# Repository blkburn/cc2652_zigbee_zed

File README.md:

# Zigbee End Device based on the CC2652R1

This is the complete hardware and software design of a zigbee end device (ZED) designed to be run from a same CR2032 button cell battery.

Texas Instruments Code Composer and the Simplelink SDK is used for development; based on the zed_temperaturesensor_CC26X2R1_LAUNCHXL_tirtos_ccs project.

The hardware design replicates the Launchpad-CC26x2R1 development board as much as possible.

The CC2652R1 is an ultra-low power ARM Cortex process with support for a number of wireless protocols, such as; Thread, Zigbee®, Bluetooth® 5.1 Low Energy, IEEE 802.15.4, IPv6-enabled (6LoWPAN), as well as proprietary protocols including TI 15.4-Stack (2.4 GHz), and simultaneous multi-protocol operation via Dynamic Multiprotocol Manager (DMM).

Development baord power consuption is in line with published datasheet power comsumption figures, allowing the zigbee end device to last many months or years on a single CR2032 battery.

The development board can interface various I2C sensors; a pin breakout is provided to interface the many cheap sensors available on-line. An Adafruit 4-pin STEMMA connector is also provide to connect to an I2C device in their range.

A JTAG header is provided to interface XDS110 (or better) debuggers. A CC1352 Launchpad with built-in XDS110 has been used to debug the development boards.

4-pin bootloader

## Master branch is currently built with:
* CCStudio version: 10.1.1.00004 
* Simplelink_cc13x2_26x2_sdk_4_30_00_54

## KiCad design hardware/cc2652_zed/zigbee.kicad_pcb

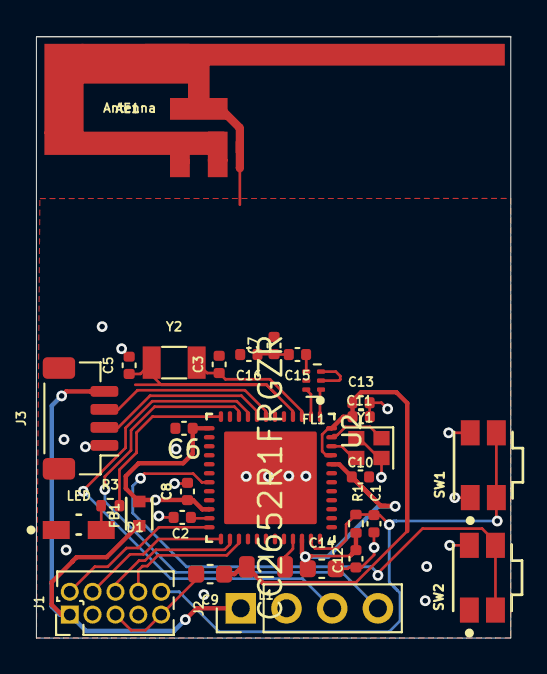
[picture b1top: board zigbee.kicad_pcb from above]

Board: 4 copper layers, 26.3 x 33.4 mm, 31 parts (1 on the bottom side), 27 nets.

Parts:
AE1: Antenna; 2.4GHz-INVERTED-F-ANTENNA
BT1: BAT-HLD-001; Linx-BAT-HLD-001-0
C1, C6, C8, C10, C11, C12, C13: 100n; C_0402_1005Metric
C2, C3, C5: 12p; C_0402_1005Metric
C7, C15, C16: CAP; C_0402_1005Metric
C9, C14: 22u; C_0603_1608Metric
D1: LED; Lite-On-LTST-S220KRKT-0-0-0
FB1: BLM18HE152SN1D; Murata-BLM18-0.15-t0.8-0-0-MFG
FL1: 2450BM14G; Balun_Johanson_1.6x0.8mm
J1: Conn_02x05_Odd_Even; PinHeader_2x05_P1.27mm_Vertical
J2: Conn_01x04; PinHeader_1x04_P2.54mm_Vertical
J3: Conn_01x04; JST_SH_BM04B-SRSS-TB_1x04-1MP_P1.00mm_Vertical
L1: L; L_0805_2012Metric
R1: 100k; R_0402_1005Metric
R3: 150; R_0402_1005Metric
SW1, SW2: EVQ-P7A01P-switch2; Panasonic-EVQ-P7A01P-0-0-MFG
U2: CC2652R1FRGZR; Texas_Instruments-CC2652R1FRGZR-MFG
Y1: Crystal_GND24; Crystal_SMD_2016-4Pin_2.0x1.6mm
Y2: Crystal; Crystal_SMD_3215-2Pin_3.2x1.5mm

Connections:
/DCDC_SW: L1.1, U2.33
/GLED: R3.2, U2.12
/RXD: J3.3, U2.7
/SCL: J2.3, U2.9
/SDA: J2.4, U2.10
/TCKC: J1.4, U2.25
/TDI: J1.8, U2.27
/TDO: J1.6, U2.26
/TMSC: J1.2, U2.24
/TXD: J3.2, U2.8
/X32K_Q1: C3.1, U2.3, Y2.1
/X32K_Q2: C5.1, U2.4, Y2.2
/nReset: C1.1, J1.10, R1.2, SW1.2, SW1.2', U2.35
GND: AE1.2, BT1.1, C1.2, C2.1, C3.2, C5.2, C6.2, C7.2, C8.2, C9.2, C10.2, C11.2, C12.2, C13.2, C14.2, D1.1, FL1.5, FL1.6, J1.3, J1.5, J1.9, J2.2, J3.1, SW1.1, SW1.1', SW2.1, SW2.1', U2.49, Y1.2, Y1.4
unnamed: AE1.1, C16.2
unnamed: C2.2, U2.23
unnamed: C15.1, FL1.1
unnamed: C7.1, C15.2, C16.1
unnamed: D1.2, R3.1
unnamed: FL1.3, U2.2
unnamed: FL1.4, U2.1
unnamed: SW2.2, SW2.2', U2.19
unnamed: U2.46, Y1.3
unnamed: U2.47, Y1.1
VDD: BT1.2, FB1.1, J1.1, J2.1, J3.4
VDDR: C9.1, C11.1, C13.1, L1.2, U2.45, U2.48
VDDS: C6.1, C8.1, C10.1, C12.1, C14.1, FB1.2, R1.1, U2.13, U2.22, U2.34, U2.44

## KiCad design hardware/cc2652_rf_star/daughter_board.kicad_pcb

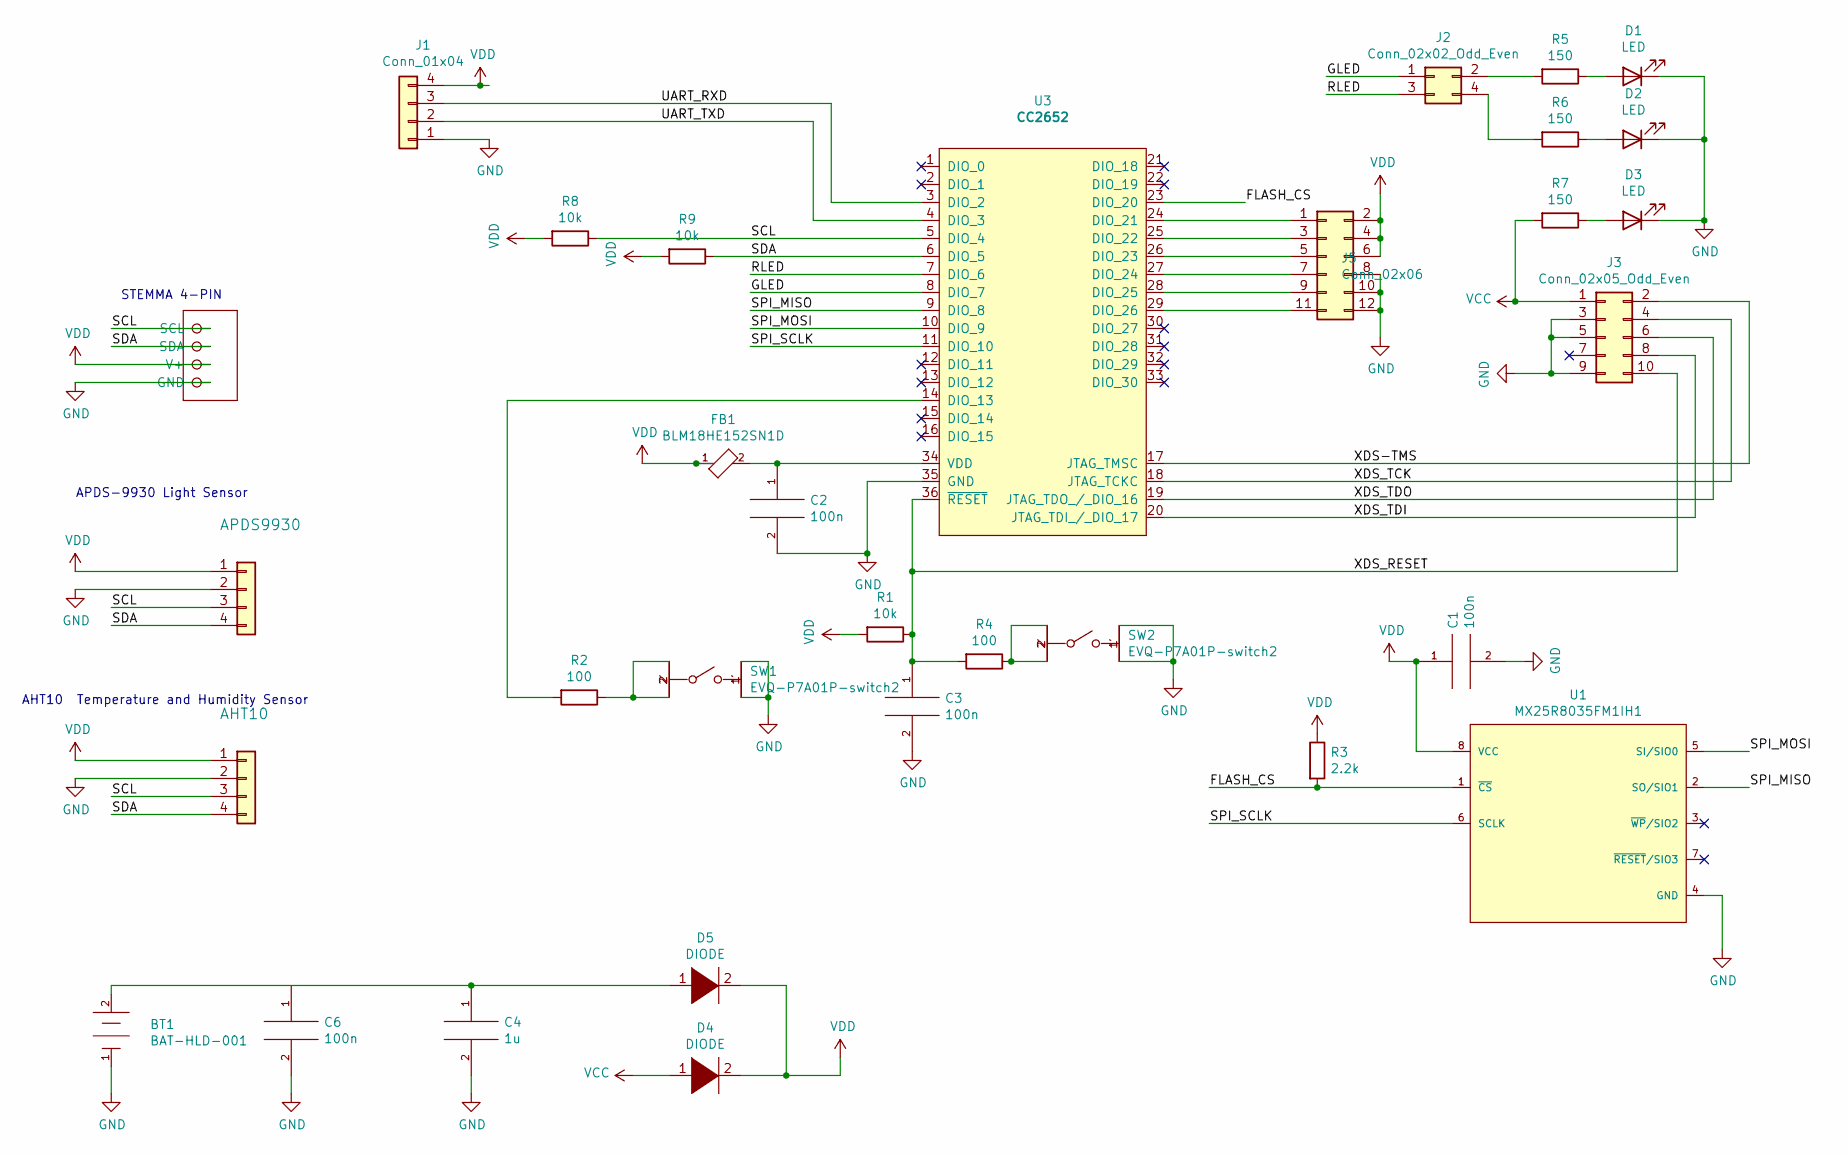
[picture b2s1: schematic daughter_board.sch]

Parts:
AHT10: Conn_01x04; PinHeader_1x04_P2.54mm_Vertical
APDS9930: Conn_01x04; PinHeader_1x04_P2.54mm_Vertical
BT1: BAT-HLD-001; Linx-BAT-HLD-001-0; mouser part number 712-BAT-HLD-001; digikey description HOLDER BATTERY 20MM COIN
C1, C2, C3, C6: 100n; C_0805_2012Metric
C4: 1u; C_0805_2012Metric
D1, D2, D3: LED; Lite-On-LTST-S220KRKT-0-0-0
D4, D5: DIODE; SOD-123FL
FB1: BLM18HE152SN1D; R_0603_1608Metric_Pad0.98x0.95mm_HandSolder; tolerance 25%
J1: Conn_01x04; PinHeader_1x04_P2.54mm_Vertical
J2: Conn_02x02_Odd_Even; PinHeader_2x02_P2.54mm_Vertical
J3: Conn_02x05_Odd_Even; PinHeader_2x05_P1.27mm_Vertical
J5: Conn_02x06; PinHeader_2x06_P2.54mm_Vertical
R1, R8, R9: 10k; R_0805_2012Metric
R2, R4: 100; R_0805_2012Metric
R3: 2.2k; R_0805_2012Metric
R5, R6, R7: 150; R_0805_2012Metric
STEMMA1: STEMMA_I2C_QT; JST_SH_BM04B-SRSS-TB_1x04-1MP_P1.00mm_Vertical
SW1, SW2: EVQ-P7A01P-switch2; Panasonic-EVQ-P7A01P-0-0-MFG; voltage rating DC 12V; mouser part number 667-EVQP7A01P; digikey description SWITCH TACTILE SPST-NO 0.05A 12V
U1: MX25R8035FM1IH1; SOP-8_3.9x4.9mm_P1.27mm; digikey description IC FLASH 8M SPI 33MHZ 8USON
U3: CC2652; rf_star_cc2652

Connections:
/FLASH_CS: R3.2, U1.1 (~CS~), U3.23 (DIO_20)
/GLED: J2.1, U3.8 (DIO_7)
/RLED: J2.3, U3.7 (DIO_6)
/SCL: AHT10.3, APDS9930.3, R8.1, STEMMA1.4 (SCL), U3.5 (DIO_4)
/SDA: AHT10.4, APDS9930.4, R9.1, STEMMA1.3 (SDA), U3.6 (DIO_5)
/SPI_MISO: U1.2 (SO/SIO1), U3.9 (DIO_8)
/SPI_MOSI: U1.5 (SI/SIO0), U3.10 (DIO_9)
/SPI_SCLK: U1.6 (SCLK), U3.11 (DIO_10)
/UART_RXD: J1.3, U3.3 (DIO_2)
/UART_TXD: J1.2, U3.4 (DIO_3)
/XDS-TMS: J3.2, U3.17 (JTAG_TMSC)
/XDS_RESET: C3.1, J3.10, R1.1, R4.2, U3.36 (~RESET)
/XDS_TCK: J3.4, U3.18 (JTAG_TCKC)
/XDS_TDI: J3.8, U3.20 (JTAG_TDI_/_DIO_17)
/XDS_TDO: J3.6, U3.19 (JTAG_TDO_/_DIO_16)
GND: AHT10.2, APDS9930.2, BT1.1 (CATHODE), C1.2, C2.2, C3.2, C4.2, C6.2, D1.1 (K), D2.1 (K), D3.1 (K), J1.1, J3.3, J3.5, J3.9, J5.8, J5.10, J5.12, STEMMA1.1 (GND), SW1.1, SW1.1', SW2.1, SW2.1', U1.4 (GND), U3.35 (GND)
unnamed: BT1.2 (ANODE), C4.1, C6.1, D5.1 (K)
unnamed: C2.1, FB1.2, U3.34 (VDD)
unnamed: D1.2 (A), R5.1
unnamed: D2.2 (A), R6.1
unnamed: D3.2 (A), R7.1
unnamed: J2.2, R5.2
unnamed: J2.4, R6.2
unnamed: J5.1, U3.24 (DIO_21)
unnamed: J5.3, U3.25 (DIO_22)
unnamed: J5.5, U3.26 (DIO_23)
unnamed: J5.7, U3.27 (DIO_24)
unnamed: J5.9, U3.28 (DIO_25)
unnamed: J5.11, U3.29 (DIO_26)
unnamed: R2.1, SW1.2, SW1.2'
unnamed: R2.2, U3.14 (DIO_13)
unnamed: R4.1, SW2.2, SW2.2'
VCC: D4.1 (K), J3.1, R7.2
VDD: AHT10.1, APDS9930.1, C1.1, D4.2 (A), D5.2 (A), FB1.1, J1.4, J5.2, J5.4, J5.6, R1.2, R3.1, R8.2, R9.2, STEMMA1.2 (V+), U1.8 (VCC)

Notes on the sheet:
STEMMA 4-PIN
APDS-9930 Light Sensor
AHT10 Temperature and Humidity Sensor

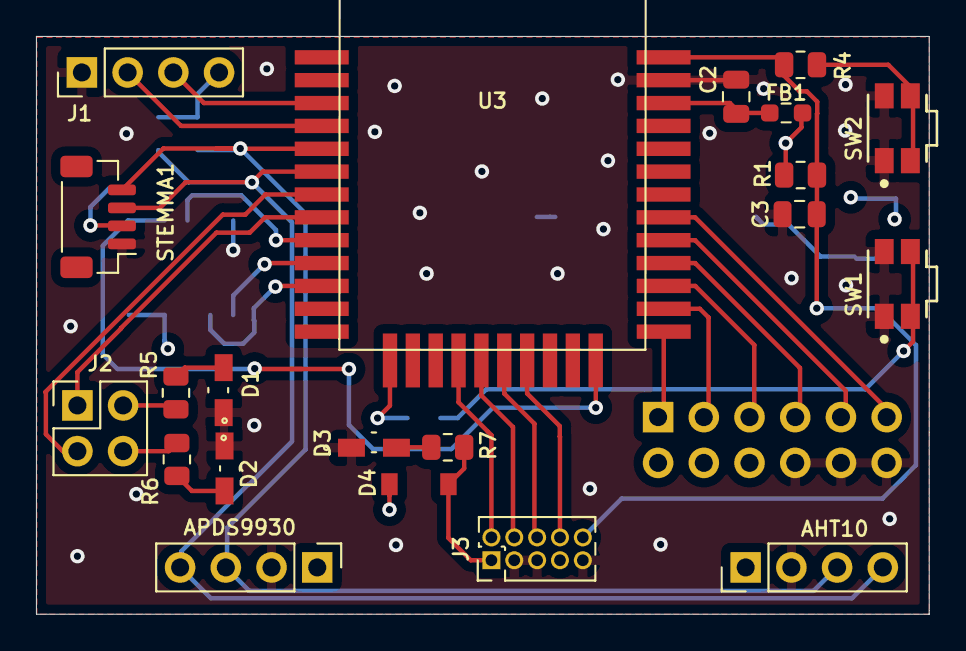
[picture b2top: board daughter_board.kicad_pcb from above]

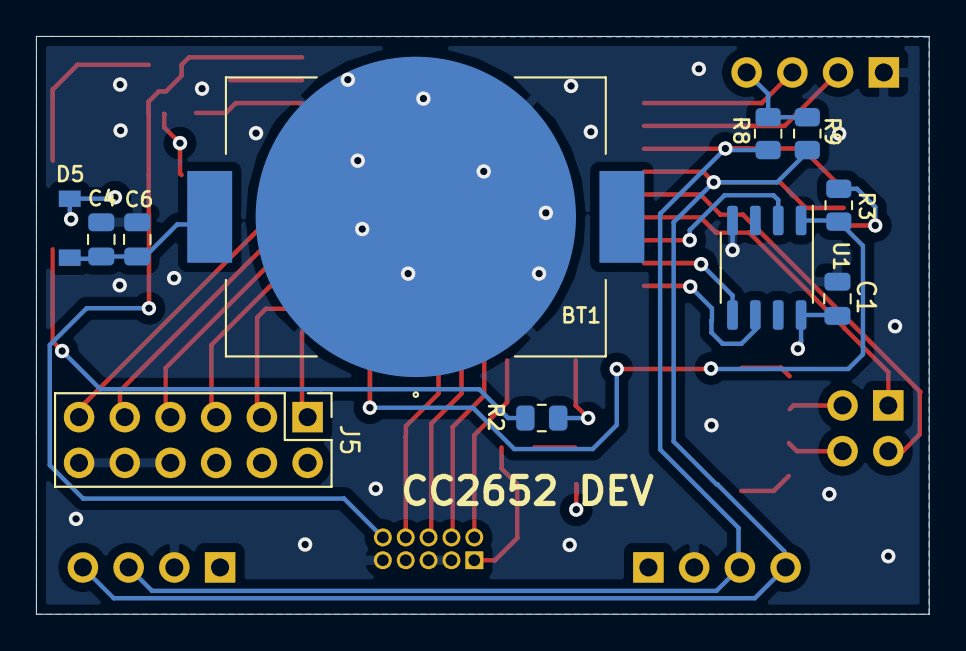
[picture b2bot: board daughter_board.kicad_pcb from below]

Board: 4 copper layers, 49.6 x 32.1 mm, 32 parts (11 on the bottom side), 34 nets.

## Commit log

2021-03-19 add license
2021-03-19 add Sensor Controller Code for the i2c sensors
2021-03-19 add ccstudio and sdk versions
2021-03-23 add kicad schematic and pcb for rf_star cc2652 daughter card
2021-03-23 add stand-alone cc2652 kicad schematic and pcb
2021-03-24 update pcb of zed add devices.js mods for zigbee2mqtt
2021-03-26 add LTR390 define to zcl_sesnor
2021-03-26 zed reports illuminance (lux) from LTR390 sensor
2021-03-29 add adps9930 light sensor to sensor controller
2021-03-29 add ALC sensor code to cc2652
2021-03-29 update apds9930 - atime 0xc0
2021-03-29 testing APDS9930
2021-03-29 update sensor controller defaults
